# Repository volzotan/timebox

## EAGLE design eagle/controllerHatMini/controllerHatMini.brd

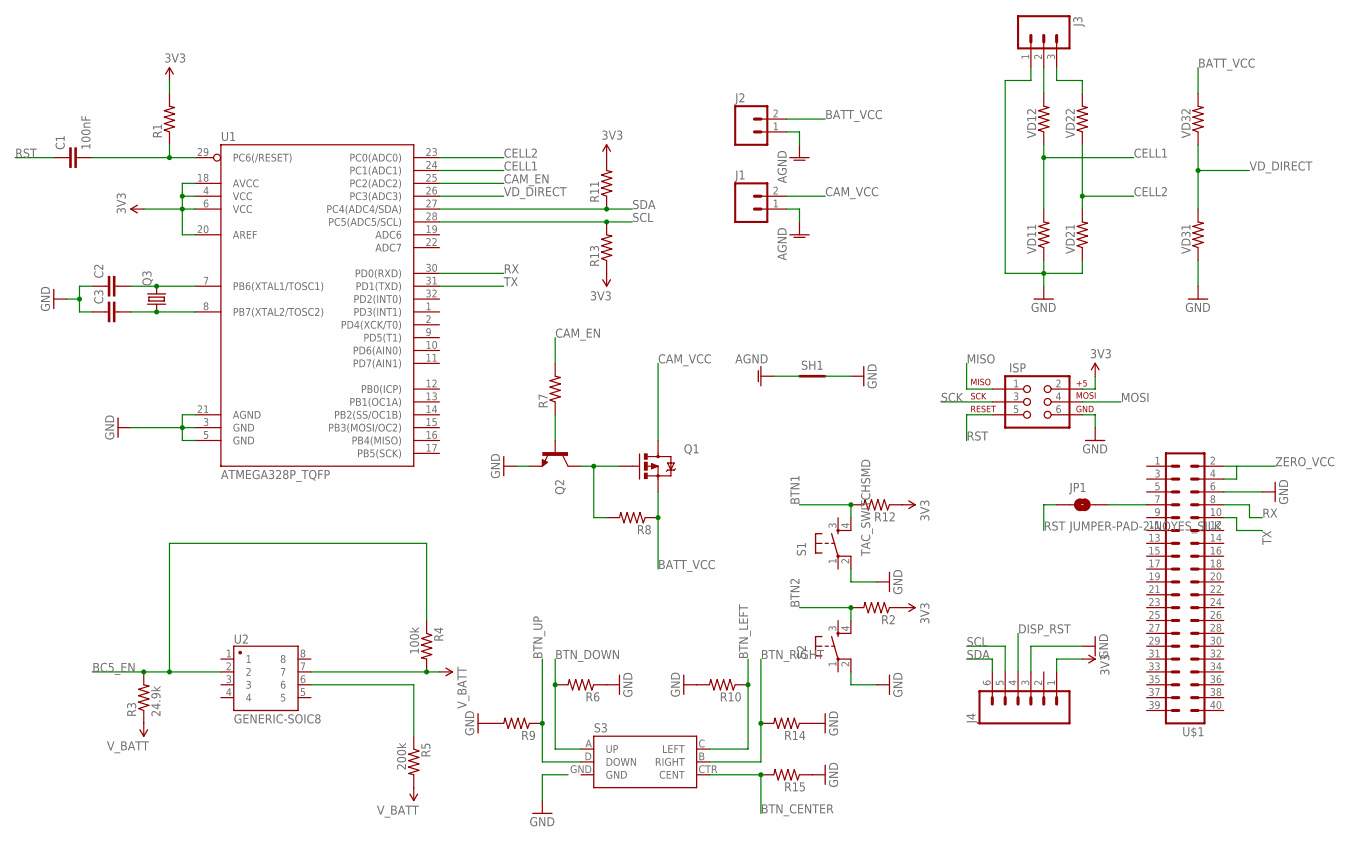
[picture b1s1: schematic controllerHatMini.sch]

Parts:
C1: 100nF; 1206
C2, C3: CAP1206; 1206
ISP: AVR_SPI_PRG_6PTH; 2X3
J1, J2: M023.5MM_LOCK; SCREWTERMINAL-3.5MM-2_LOCK
J3: M03LOCK; 1X03_LOCK
J4: M06LOCK; 1X06_LOCK
JP1: JUMPER-PAD-2-NOYES_SILK; PAD-JUMPER-2-NO_YES_SILK
Q1: MOSFET-PCHANNELNDP6020P_20V_24A_LOW_VGS_TH; TO220V
Q2: TRANSISTOR_NPN2N3904; TO-92
Q3: CRYSTALMM20SS; MM20SS
R1, R2, R6, R7, R8, R9, R10, R11, R12, R13, R14, R15: RESISTOR1206; 1206
R3: 24.9k; 1206
R4: 100k; 1206
R5: 200k; 1206
S1: TAC_SWITCHSMD; TACTILE-PTH
S2: TAC_SWITCHPTH; TACTILE-PTH
S3: JOYSTICK_MINI
SH1: SHORT-HT5; SHORT_TOP-50
U1: ATMEGA328P_TQFP; TQFP32-08
U2: GENERIC-SOIC8; SO08-UNIVERSAL
U$1: PIZERO_THROUGH_HOLE; PIZERO_THOUGH_HOLE
VD11, VD12, VD21, VD22, VD31, VD32: RESISTOR1206; 1206

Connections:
AGND: J1.1, J2.1, SH1.1
BATT_VCC: J2.2, Q1.3 (S), R8.1, VD32.2
BC5_EN: R3.2, R4.1, U2.2
BTN1: R12.2, S1.4
BTN2: R2.2, S2.4
BTN_CENTER: R15.2, S3.CTR (CENT)
BTN_DOWN: R6.2, S3.A (UP)
BTN_LEFT: R10.1, S3.C (LEFT)
BTN_RIGHT: R14.2, S3.B (RIGHT)
BTN_UP: R9.1, S3.D (DOWN)
CAM_EN: R7.2, U1.25 (PC2(ADC2))
CAM_VCC: J1.2, Q1.2 (D)
CELL1: U1.24 (PC1(ADC1)), VD11.2, VD12.1
CELL2: U1.23 (PC0(ADC0)), VD21.2, VD22.1
DISP_RST: J4.4
GND: C2.1, C3.1, ISP.6, J3.1, J4.3, Q2.1 (E), R6.1, R9.2, R10.2, R14.1, R15.1, S1.2, S2.2, SH1.2, U1.3 (GND), U1.5 (GND), U1.21 (AGND), U$1.6, VD11.1, VD21.1, VD31.1
MISO: ISP.1
MOSI: ISP.4
unnamed: J3.3, VD22.2
unnamed: J3.2, VD12.2
unnamed: C1.2, R1.1, U1.29 (PC6(/RESET))
unnamed: Q2.2 (B), R7.1
unnamed: C3.2, Q3.1, U1.8 (PB7(XTAL2/TOSC2))
unnamed: C2.2, Q3.4 (2), U1.7 (PB6(XTAL1/TOSC1))
unnamed: JP1.2, U$1.7
unnamed: Q1.1 (G), Q2.3 (C), R8.2
unnamed: R5.1, U2.6
RST: C1.1, ISP.5, JP1.1
RX: U1.30 (PD0(RXD)), U$1.8
SCK: ISP.3
SCL: J4.5, R13.2, U1.28 (PC5(ADC5/SCL))
SDA: J4.6, R11.1, U1.27 (PC4(ADC4/SDA))
TX: U1.31 (PD1(TXD)), U$1.10
VCC: ISP.2, J4.1, R1.2, R2.1, R11.2, R12.1, R13.1, U1.4 (VCC), U1.6 (VCC), U1.18 (AVCC), U1.20 (AREF)
VD_DIRECT: U1.26 (PC3(ADC3)), VD31.2, VD32.1
V_BATT: R3.1, R4.2, R5.2, U2.7
ZERO_VCC: U$1.2

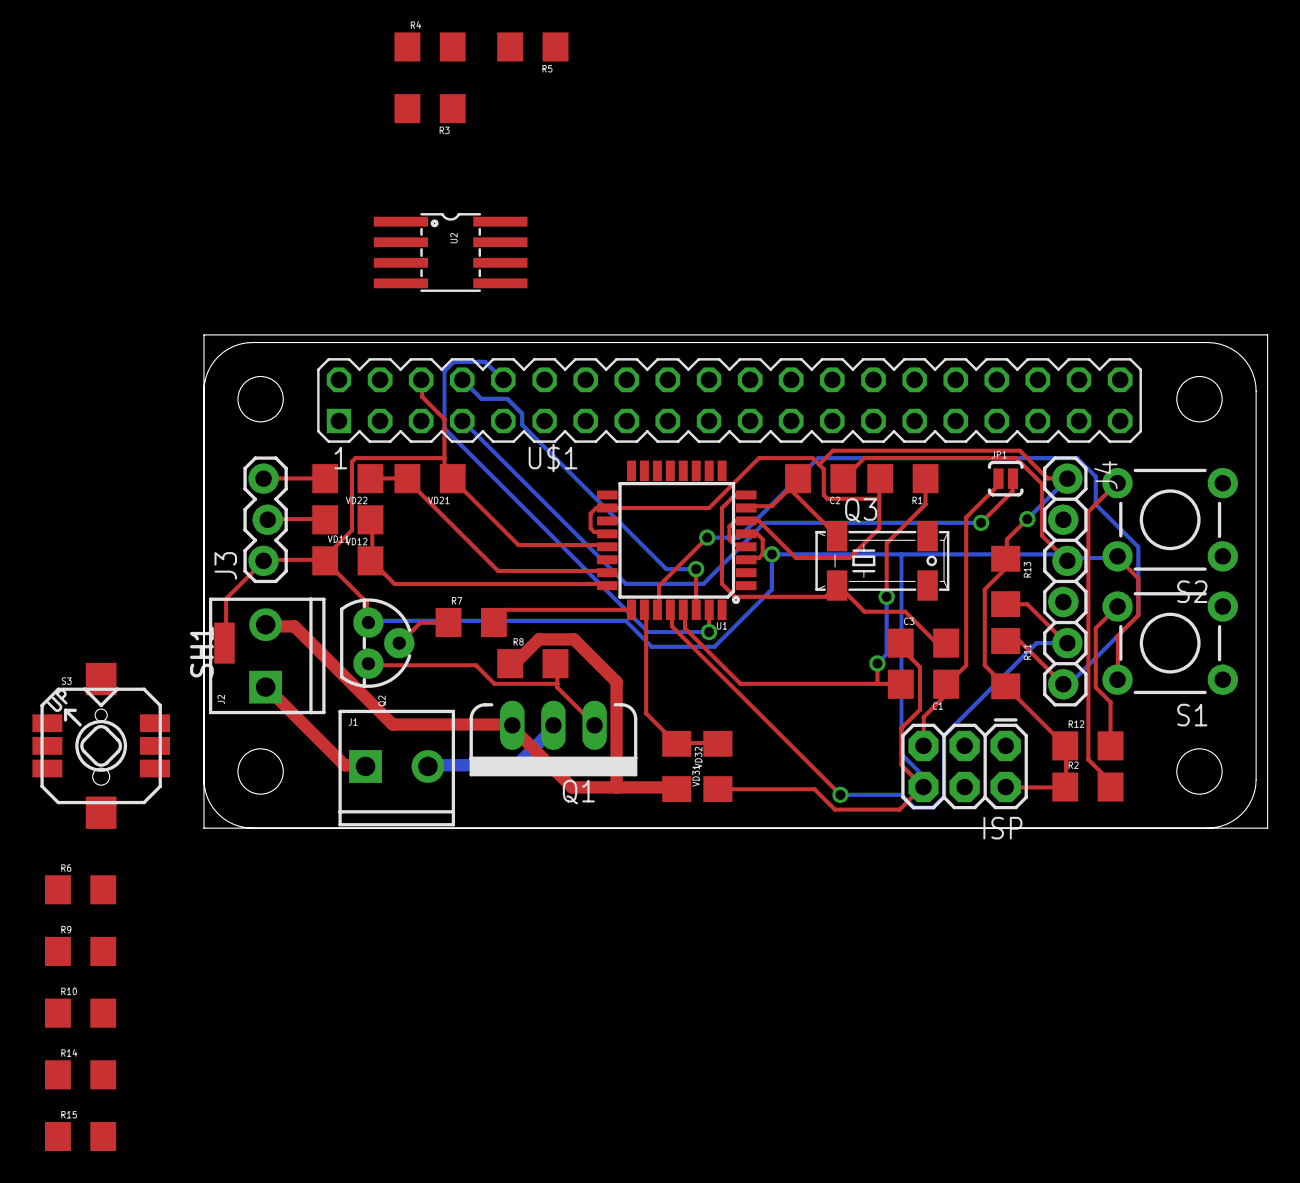
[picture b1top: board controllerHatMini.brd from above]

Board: 2 copper layers, 65.7 x 30.5 mm, 40 parts (0 on the bottom side), 32 nets.

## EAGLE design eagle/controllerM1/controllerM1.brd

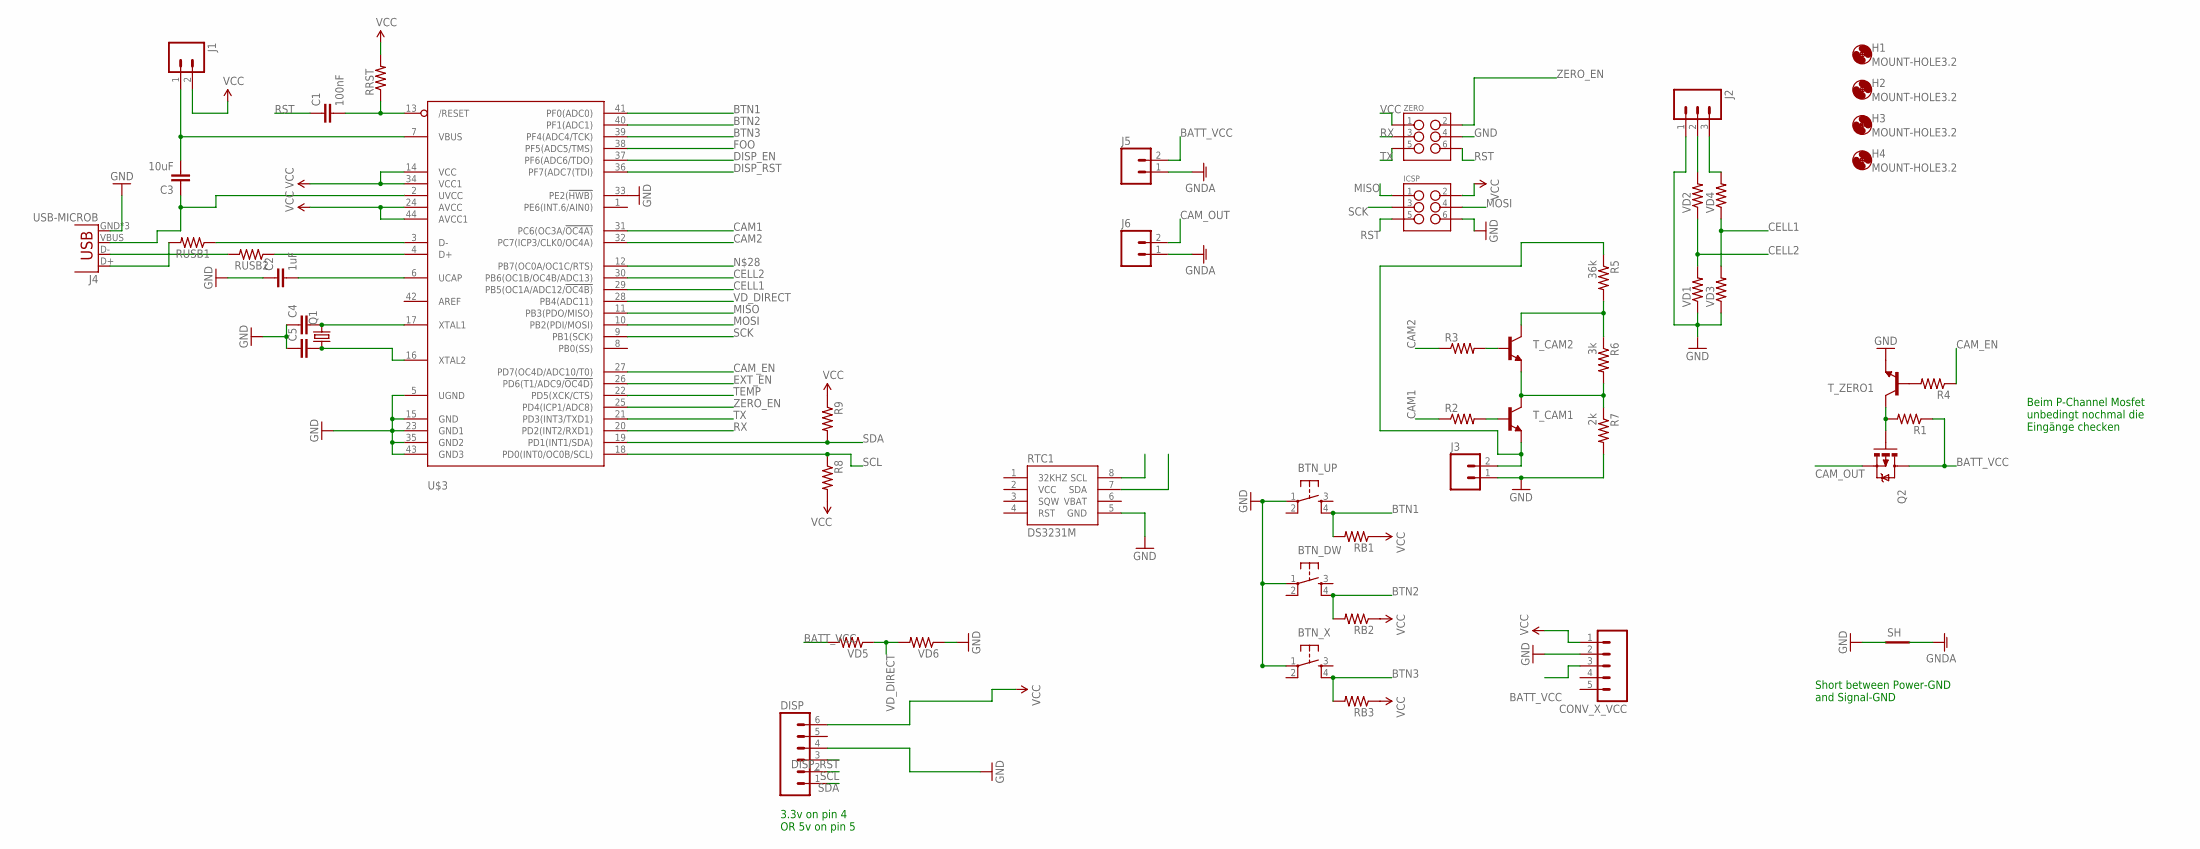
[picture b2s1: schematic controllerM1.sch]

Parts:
BTN_DW: TAC_SWITCHPTH; TACTILE-PTH
BTN_UP: TAC_SWITCHPTH; TACTILE-PTH
BTN_X: TAC_SWITCHPTH; TACTILE-PTH
C1: 100nF; 1206
C2: 1uF; 1206
C3: 10uF; 1206
C4, C5: CAP1206; 1206
CONV_X_VCC: M05LOCK; 1X05_LOCK
DISP: M06FEMALE_LOCK; 1X06_FEMALE_LOCK.010
H1, H2, H3, H4: MOUNT-HOLE3.2; 3,2
ICSP: M03X2FEMALE; 2X3
J1, J3: M02LOCK; 1X02_LOCK
J2: M03LOCK; 1X03_LOCK
J4: USB-MICROB
J5, J6: M023.5MM_LOCK; SCREWTERMINAL-3.5MM-2_LOCK
Q1: CRYSTALHC49S; HC49/S
Q2: MOSFET-PCHANNELFQP27P06; TO220V
R1, R2, R3, R4, R8, R9: RESISTOR1206; 1206
R5: 36k; 1206
R6: 3k; 1206
R7: 2k; 1206
RB1, RB2, RB3: RESISTOR1206; 1206
RRST: RESISTOR1206; 1206
RTC1: DS3231M; SOIC8
RUSB1, RUSB2: RESISTOR1206; 1206
SH: SHORT-HT5; SHORT_TOP-50
T_CAM1, T_CAM2: TRANSISTOR_NPN2N3904; TO-92
T_ZERO1: TRANSISTOR_NPN2N3904; TO-92
U$3: ATMEGA32U4-AU; TQFP44
VD1, VD2, VD3, VD4, VD5, VD6: RESISTOR1206; 1206
ZERO: M03X2FEMALE; 2X3

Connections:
BATT_VCC: CONV_X_VCC.3, J5.2, Q2.2 (D), R1.1, VD5.2
BTN1: BTN_UP.4, RB1.2, U$3.41 (PF0(ADC0))
BTN2: BTN_DW.4, RB2.2, U$3.40 (PF1(ADC1))
BTN3: BTN_X.4, RB3.2, U$3.39 (PF4(ADC4/TCK))
CAM1: R2.1, U$3.31 (PC6(OC3A/!OC4A))
CAM2: R3.1, U$3.32 (PC7(ICP3/CLK0/OC4A))
CAM_EN: R4.1, U$3.27 (PD7(OC4D/ADC10/T0))
CAM_OUT: J6.2, Q2.3 (S)
CELL1: U$3.29 (PB5(OC1A/ADC12/!OC4B)), VD3.2, VD4.1
CELL2: U$3.30 (PB6(OC1B/OC4B/ADC13)), VD1.2, VD2.1
DISP_EN: U$3.37 (PF6(ADC6/TDO))
DISP_RST: DISP.3, U$3.36 (PF7(ADC7(TDI))
EXT_EN: U$3.26 (PD6(T1/ADC9/!OC4D))
FOO: U$3.38 (PF5(ADC5/TMS))
GND: BTN_DW.1, BTN_UP.1, BTN_X.1, C2.1, C4.1, C5.1, CONV_X_VCC.2, DISP.4, ICSP.6, J2.1, J3.1, J4.GND, J4.MT1 (GND), J4.MT2 (GND), R7.2, RTC1.5 (GND), SH.1, T_ZERO1.1 (E), U$3.5 (UGND), U$3.15 (GND), U$3.23 (GND1), U$3.33 (PE2(!HWB)), U$3.35 (GND2), U$3.43 (GND3), VD1.1, VD3.1, VD6.1, ZERO.4
GNDA: J5.1, J6.1, SH.2
MISO: ICSP.1, U$3.11 (PB3(PDO/MISO))
MOSI: ICSP.4, U$3.10 (PB2(PDI/MOSI))
unnamed: C1.2, RRST.1, U$3.13 (/RESET)
unnamed: J2.3, VD4.2
unnamed: J2.2, VD2.2
unnamed: RUSB1.1, U$3.3 (D-)
unnamed: RUSB2.1, U$3.4 (D+)
unnamed: J3.2, R5.1, T_CAM1.1 (E)
unnamed: R4.2, T_ZERO1.2 (B)
unnamed: C4.2, Q1.2, U$3.17 (XTAL1)
unnamed: C5.2, Q1.1, U$3.16 (XTAL2)
unnamed: C3.2, J1.1, U$3.7 (VBUS)
unnamed: R6.2, R7.1, T_CAM1.3 (C), T_CAM2.1 (E)
unnamed: R5.2, R6.1, T_CAM2.3 (C)
unnamed: J4.D+, RUSB1.2
unnamed: J4.D-, RUSB2.2
unnamed: R2.2, T_CAM1.2 (B)
unnamed: R3.2, T_CAM2.2 (B)
unnamed: C2.2, U$3.6 (UCAP)
unnamed: Q2.1 (G), R1.2, T_ZERO1.3 (C)
unnamed: C3.1, J4.VBUS, U$3.2 (UVCC)
RST: C1.1, ICSP.5, ZERO.6
RX: U$3.20 (PD2(INT2/RXD1)), ZERO.3
SCK: ICSP.3, U$3.9 (PB1(SCK))
SCL: DISP.2, R8.1, RTC1.8 (SCL), U$3.18 (PD0(INT0/OC0B/SCL))
SDA: DISP.1, R9.2, RTC1.7 (SDA), U$3.19 (PD1(INT1/SDA))
TEMP: U$3.22 (PD5(XCK/CTS))
TX: U$3.21 (PD3(INT3/TXD1)), ZERO.5
VBAT: RTC1.6 (VBAT)
VCC: CONV_X_VCC.1, DISP.6, ICSP.2, J1.2, R8.2, R9.1, RB1.1, RB2.1, RB3.1, RRST.2, RTC1.2 (VCC), U$3.14 (VCC), U$3.24 (AVCC), U$3.34 (VCC1), U$3.44 (AVCC1), ZERO.1
VD_DIRECT: U$3.28 (PB4(ADC11)), VD5.1, VD6.2
ZERO_EN: U$3.25 (PD4(ICP1/ADC8)), ZERO.2

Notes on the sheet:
3.3v on pin 4 OR 5v on pin 5
Short between Power-GND and Signal-GND
Beim P-Channel Mosfet unbedingt nochmal die Eingänge checken

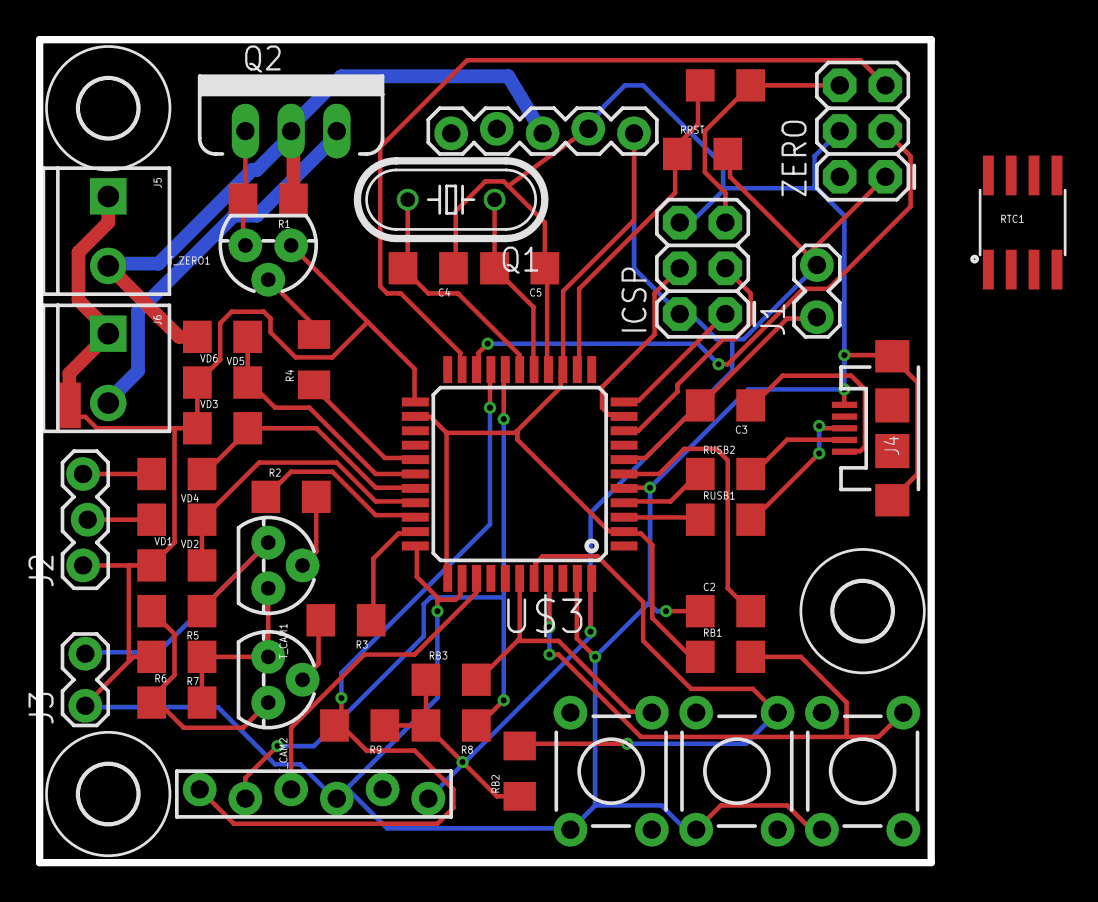
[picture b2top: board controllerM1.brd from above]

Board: 2 copper layers, 49.5 x 45.7 mm, 51 parts (0 on the bottom side), 43 nets.

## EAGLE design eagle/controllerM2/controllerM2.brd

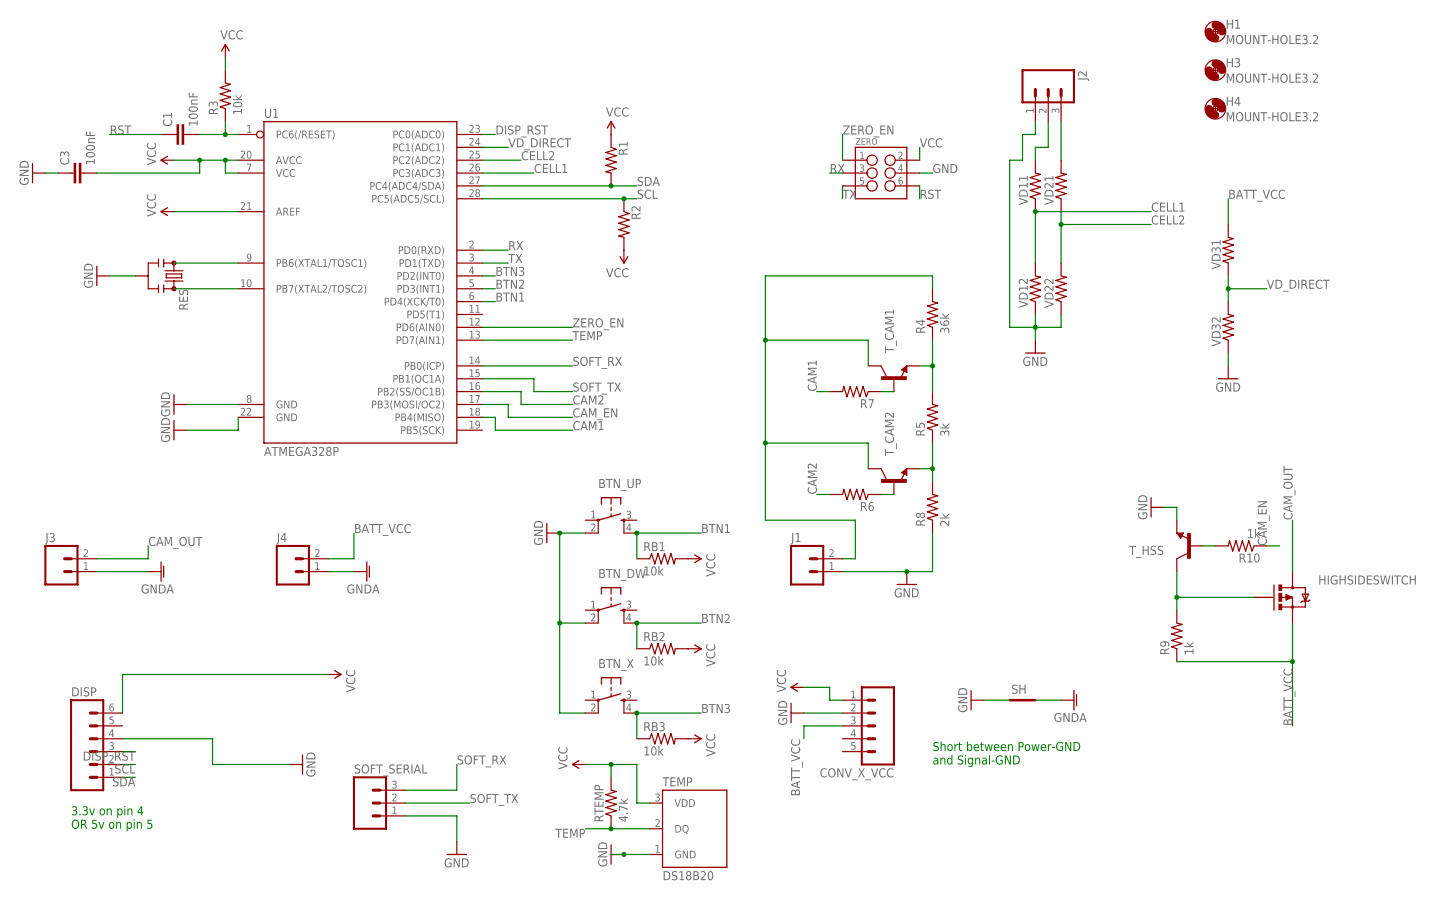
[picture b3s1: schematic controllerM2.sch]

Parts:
BTN_DW: TAC_SWITCHPTH; TACTILE-PTH
BTN_UP: TAC_SWITCHPTH; TACTILE-PTH
BTN_X: TAC_SWITCHPTH; TACTILE-PTH
C1, C3: 100nF; CAP-PTH-SMALL
CONV_X_VCC: M05LOCK; 1X05_LOCK
DISP: M06FEMALE_LOCK; 1X06_FEMALE_LOCK.010
H1, H3, H4: MOUNT-HOLE3.2; 3,2
HIGHSIDESWITCH: MOSFET-PCHANNELNDP6020P_20V_24A_LOW_VGS_TH; TO220V
J1: M02LOCK; 1X02_LOCK
J2: M03LOCK; 1X03_LOCK
J3, J4: M023.5MM_LOCK; SCREWTERMINAL-3.5MM-2_LOCK
R1, R2, R6, R7: RESISTORAXIAL-0.3; AXIAL-0.3
R3: 10k; AXIAL-0.3
R4: 36k; AXIAL-0.3
R5: 3k; AXIAL-0.3
R8: 2k; AXIAL-0.3
R9, R10: 1k; AXIAL-0.3
RB1, RB2, RB3: 10k; AXIAL-0.3
RES: RESONATORPTH; RESONATOR-PTH
RTEMP: 4.7k; AXIAL-0.3
SH: SHORT-HT5; SHORT_TOP-50
SOFT_SERIAL: M03LOCK; 1X03_LOCK
TEMP: DS18B20; TO-92-AMMO
T_CAM1, T_CAM2: TRANSISTOR_NPN2N3904; TO-92
T_HSS: TRANSISTOR_NPN2N3904; TO-92
U1: ATMEGA328P; DIL28-3
VD11, VD12, VD21, VD22, VD31, VD32: RESISTORAXIAL-0.3; AXIAL-0.3
ZERO: M03X2FEMALE; 2X3

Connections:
BATT_VCC: CONV_X_VCC.3, HIGHSIDESWITCH.3 (S), J4.2, R9.P$1 (1), VD31.P$2 (2)
BTN1: BTN_UP.4, RB1.P$1 (1), U1.6 (PD4(XCK/T0))
BTN2: BTN_DW.4, RB2.P$1 (1), U1.5 (PD3(INT1))
BTN3: BTN_X.4, RB3.P$1 (1), U1.4 (PD2(INT0))
CAM1: R7.P$2 (2), U1.18 (PB4(MISO))
CAM2: R6.P$2 (2), U1.16 (PB2(SS/OC1B))
CAM_EN: R10.P$1 (1), U1.17 (PB3(MOSI/OC2))
CAM_OUT: HIGHSIDESWITCH.2 (D), J3.2
CELL1: U1.26 (PC3(ADC3)), VD11.P$1 (1), VD12.P$2 (2)
CELL2: U1.25 (PC2(ADC2)), VD21.P$1 (1), VD22.P$2 (2)
DISP_RST: DISP.3, U1.23 (PC0(ADC0))
GND: BTN_DW.2, BTN_UP.2, BTN_X.2, C3.1, CONV_X_VCC.2, DISP.4, J1.1, J2.1, R8.P$1 (1), RES.2, SH.1, SOFT_SERIAL.1, TEMP.1 (GND), T_HSS.1 (E), U1.8 (GND), U1.22 (GND), VD12.P$1 (1), VD22.P$1 (1), VD32.P$1 (1), ZERO.4
GNDA: J3.1, J4.1, SH.2
unnamed: C1.2, R3.P$1 (1), U1.1 (PC6(/RESET))
unnamed: J2.2, VD11.P$2 (2)
unnamed: R7.P$1 (1), T_CAM1.2 (B)
unnamed: J2.3, VD21.P$2 (2)
unnamed: J1.2, R4.P$2 (2), T_CAM1.3 (C), T_CAM2.3 (C)
unnamed: RES.3, U1.10 (PB7(XTAL2/TOSC2))
unnamed: RES.1, U1.9 (PB6(XTAL1/TOSC1))
unnamed: R6.P$1 (1), T_CAM2.2 (B)
unnamed: R10.P$2 (2), T_HSS.2 (B)
unnamed: HIGHSIDESWITCH.1 (G), R9.P$2 (2), T_HSS.3 (C)
unnamed: R4.P$1 (1), R5.P$2 (2), T_CAM1.1 (E)
unnamed: R5.P$1 (1), R8.P$2 (2), T_CAM2.1 (E)
RST: C1.1, ZERO.6
RX: U1.2 (PD0(RXD)), ZERO.3
SCL: DISP.2, R2.P$1 (1), U1.28 (PC5(ADC5/SCL))
SDA: DISP.1, R1.P$2 (2), U1.27 (PC4(ADC4/SDA))
SOFT_RX: SOFT_SERIAL.3, U1.14 (PB0(ICP))
SOFT_TX: SOFT_SERIAL.2, U1.15 (PB1(OC1A))
TEMP: RTEMP.P$1 (1), TEMP.2 (DQ), U1.13 (PD7(AIN1))
TX: U1.3 (PD1(TXD)), ZERO.5
VCC: C3.2, CONV_X_VCC.1, DISP.6, R1.P$1 (1), R2.P$2 (2), R3.P$2 (2), RB1.P$2 (2), RB2.P$2 (2), RB3.P$2 (2), RTEMP.P$2 (2), TEMP.3 (VDD), U1.7 (VCC), U1.20 (AVCC), U1.21 (AREF), ZERO.2
VD_DIRECT: U1.24 (PC1(ADC1)), VD31.P$1 (1), VD32.P$2 (2)
ZERO_EN: U1.12 (PD6(AIN0)), ZERO.1

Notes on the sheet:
3.3v on pin 4 OR 5v on pin 5
Short between Power-GND and Signal-GND

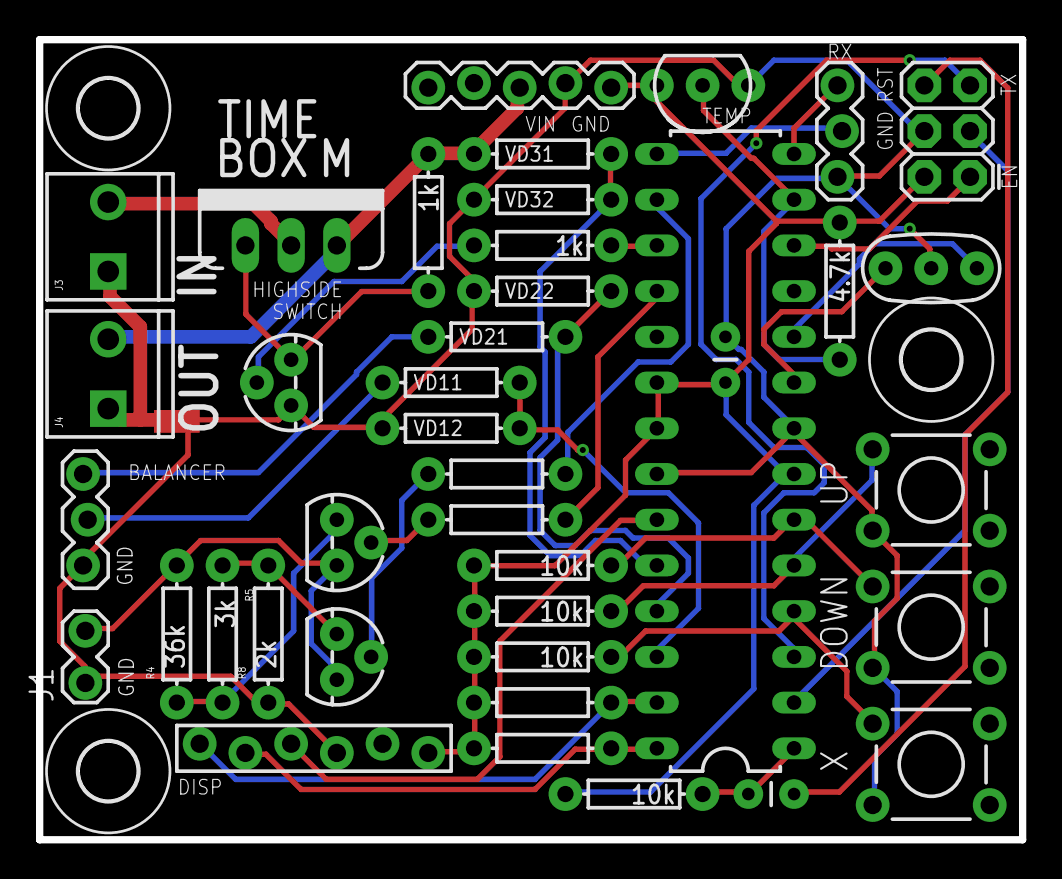
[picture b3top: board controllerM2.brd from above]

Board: 2 copper layers, 54.6 x 44.5 mm, 44 parts (0 on the bottom side), 36 nets.

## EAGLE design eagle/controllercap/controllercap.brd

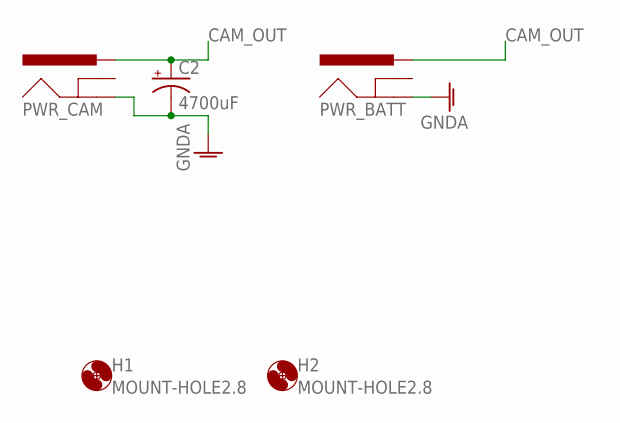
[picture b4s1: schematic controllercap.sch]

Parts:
C2: 4700uF; CPOL-RADIAL-1000UF-63V
H1, H2: MOUNT-HOLE2.8; 2,8
PWR_BATT: POWER_JACKPTH_BREAD; POWER_JACK_PTH_BREAD
PWR_CAM: POWER_JACKPTH_BREAD; POWER_JACK_PTH_BREAD

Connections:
CAM_OUT: C2.1 (+), PWR_BATT.PWR, PWR_CAM.PWR
GNDA: C2.2 (-), PWR_BATT.GND, PWR_CAM.GND

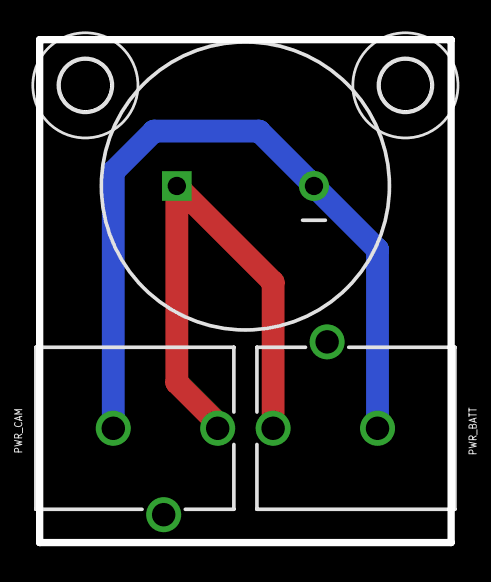
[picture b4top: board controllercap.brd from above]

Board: 2 copper layers, 22.9 x 27.9 mm, 5 parts (0 on the bottom side), 2 nets.

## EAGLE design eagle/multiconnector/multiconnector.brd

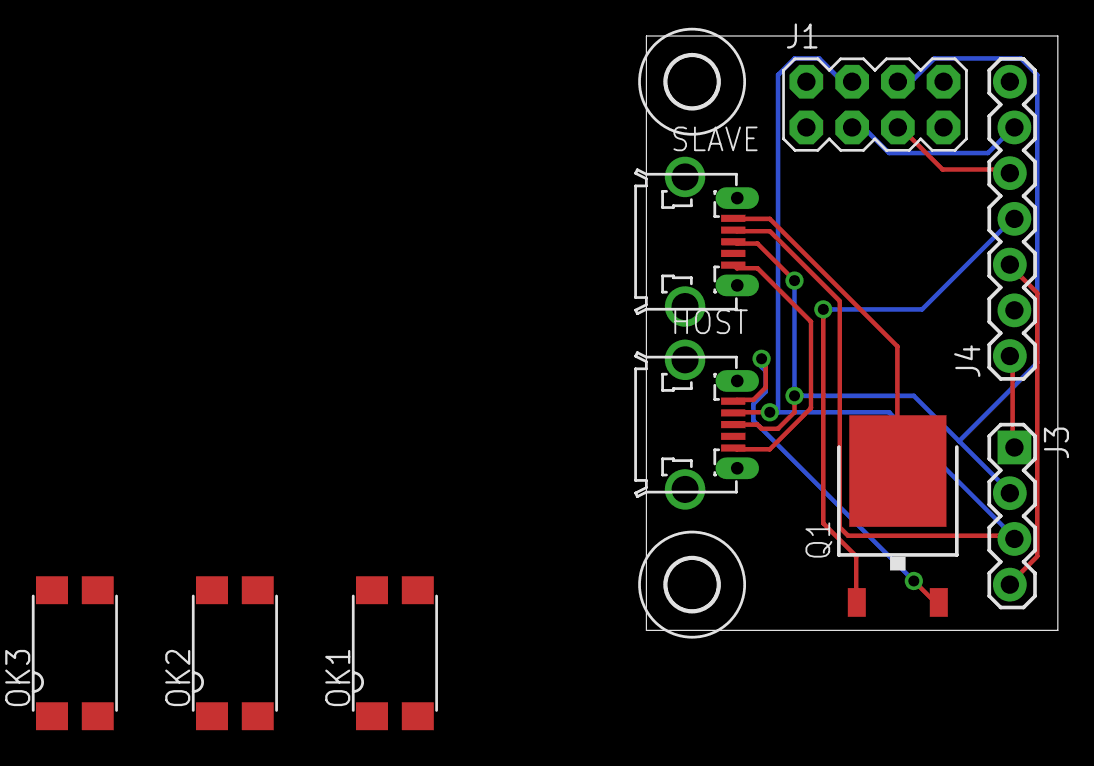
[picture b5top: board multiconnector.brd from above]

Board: 2 copper layers, 22.9 x 33.0 mm, 11 parts (0 on the bottom side), 10 nets.

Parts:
H1, H2: MOUNT-HOLE2.8; 2,8
HOST: ZX62D-B-5PA8
J1: 2X4
J3: 1X04_LOCK
J4: 1X07_LOCK
OK1, OK2, OK3: LTV816S; SMD4
Q1: FDD4141TO252; TO252
SLAVE: ZX62D-B-5PA8

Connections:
CAM2: J1.3, J4.6
CAM3: J1.5, J4.5
D+: HOST.2, J1.4, J3.3, SLAVE.2
D-: HOST.3, J1.6, J3.2, SLAVE.3
GND: J3.1, J4.1
HOST_VCC: HOST.1, Q1.2
unnamed: HOST.5, SLAVE.5
SLAVE_VCC: Q1.3, SLAVE.1
VCC: J3.4, J4.3
VCC_EN: J4.4, Q1.1

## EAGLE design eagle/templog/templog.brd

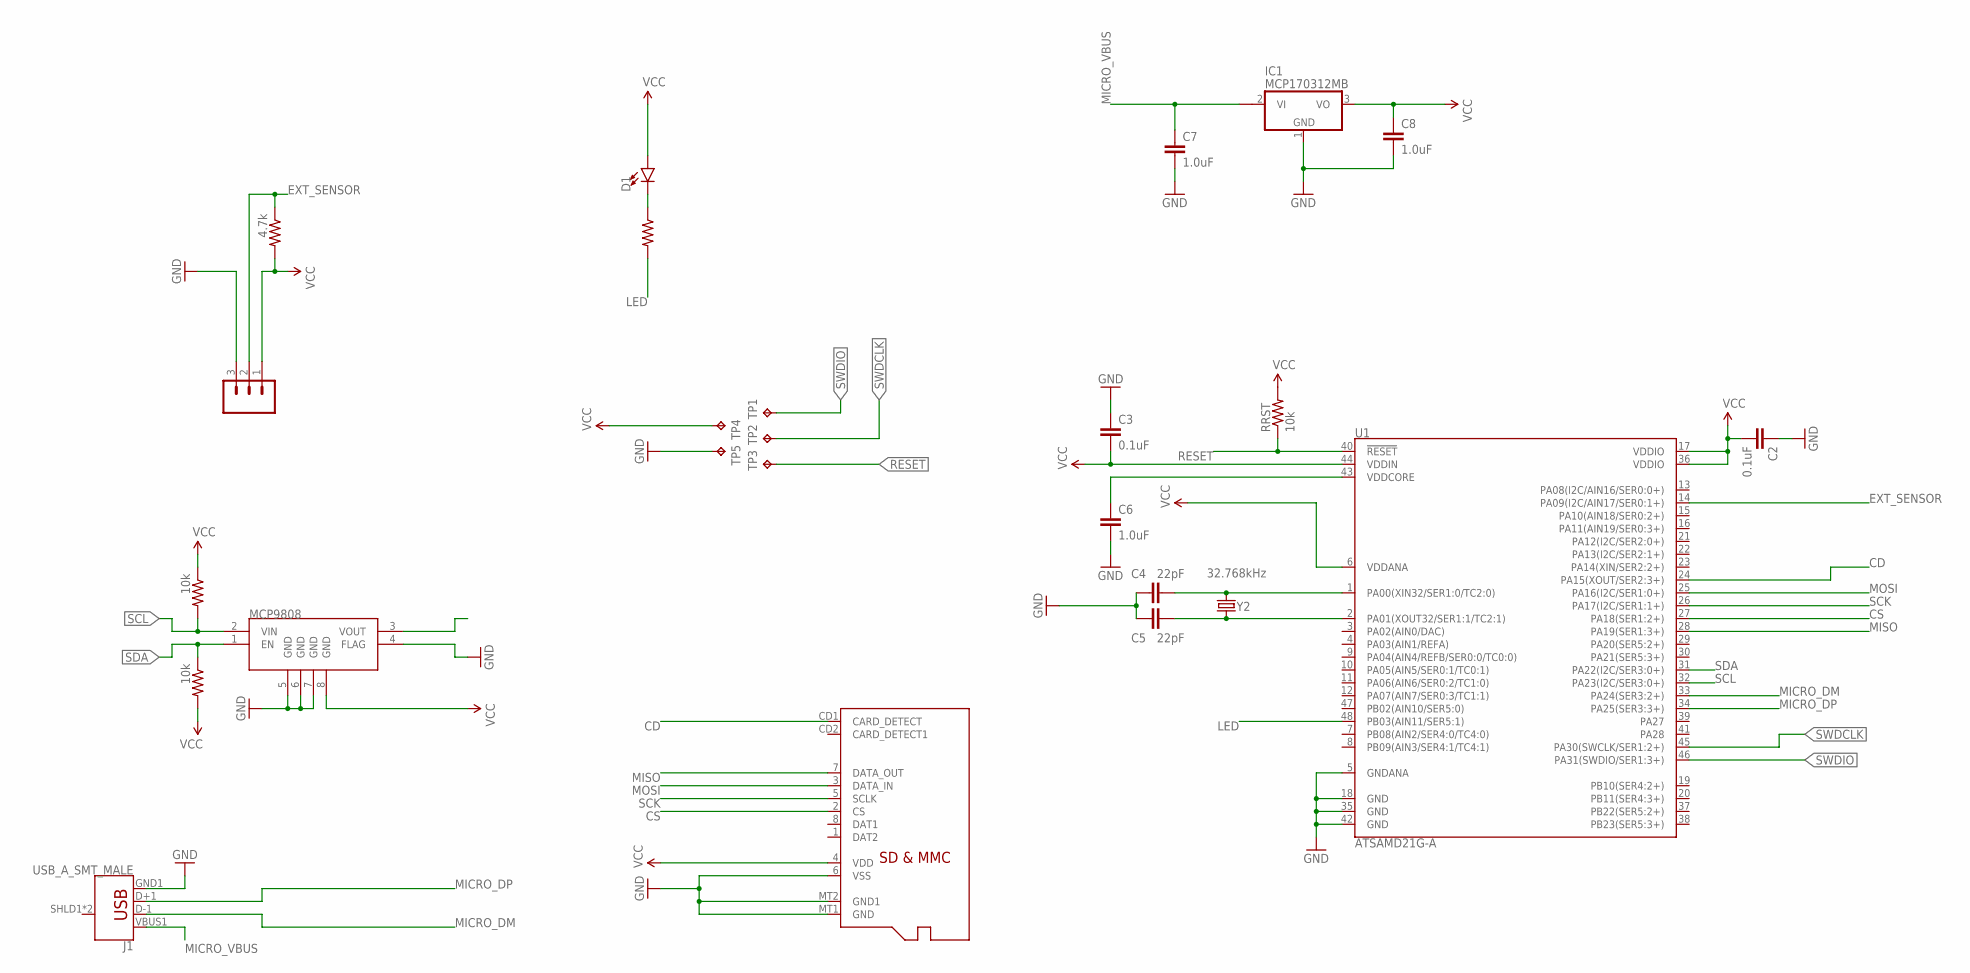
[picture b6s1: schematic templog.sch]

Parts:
C2, C3: 0.1uF; 0805
C4, C5: 22pF; 0805
C6, C7, C8: 1.0uF; 0805
D1: LED1206; LED-1206
IC1: MCP170312MB; SOT89
J1: USB_A_SMT_MALE; USB-A-SMT-MALE
J2: CONN_03SMD; 1X03-1MM-RA
MCP9808: V_REG_MIC5216; MSOP8
RRST: 10k; 0805
R_I2C_1, R_I2C_2: 10k; 0805
R_I2C_3: 4.7k; 0805
R_I2C_4: RESISTOR0805-RES; 0805
TP1, TP2, TP3, TP4, TP5: TPB1,27; B1,27
U1: ATSAMD21G-A; TQFP-48
U$1: MICROSD
Y2: 32.768kHz; CRYSTAL-SMD-3.2X1.5MM

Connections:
CD: U1.24 (PA15(XOUT/SER2:3+)), U$1.CD1 (CARD_DETECT)
CS: U1.27 (PA18(SER1:2+)), U$1.2 (CS)
EXT_SENSOR: J2.2, R_I2C_3.1, U1.14 (PA09(I2C/AIN17/SER0:1+))
GND: C2.1, C3.1, C4.1, C5.1, C6.2, C7.2, C8.2, IC1.1 (GND), J1.GND1 (GND), J2.3, MCP9808.4 (FLAG), MCP9808.5 (GND), MCP9808.6 (GND), MCP9808.7 (GND), TP5.TP, U1.5 (GNDANA), U1.18 (GND), U1.35 (GND), U1.42 (GND), U$1.6 (VSS), U$1.MT1 (GND), U$1.MT2 (GND1)
LED: R_I2C_4.2, U1.48 (PB03(AIN11/SER5:1))
MICRO_DM: J1.D-1 (D-), U1.33 (PA24(SER3:2+))
MICRO_DP: J1.D+1 (D+), U1.34 (PA25(SER3:3+))
MICRO_VBUS: C7.1, IC1.2@1 (VI1), J1.VBUS1 (VBUS)
MISO: U1.28 (PA19(SER1:3+)), U$1.7 (DATA_OUT)
MOSI: U1.25 (PA16(I2C/SER1:0+)), U$1.3 (DATA_IN)
unnamed: C6.1, U1.43 (VDDCORE)
unnamed: D1.C, R_I2C_4.1
unnamed: C4.2, U1.1 (PA00(XIN32/SER1:0/TC2:0)), Y2.P$2 (2)
unnamed: C5.2, U1.2 (PA01(XOUT32/SER1:1/TC2:1)), Y2.P$1 (1)
RESET: RRST.1, TP3.TP, U1.40 (!RESET!)
SCK: U1.26 (PA17(I2C/SER1:1+)), U$1.5 (SCLK)
SCL: MCP9808.2 (VIN), R_I2C_1.2, U1.32 (PA23(I2C/SER3:0+))
SDA: MCP9808.1 (EN), R_I2C_2.1, U1.31 (PA22(I2C/SER3:0+))
SWDCLK: TP2.TP, U1.45 (PA30(SWCLK/SER1:2+))
SWDIO: TP1.TP, U1.46 (PA31(SWDIO/SER1:3+))
VCC: C2.2, C3.2, C8.1, D1.A, IC1.3 (VO), J2.1, MCP9808.8 (GND), RRST.2, R_I2C_1.1, R_I2C_2.2, R_I2C_3.2, TP4.TP, U1.6 (VDDANA), U1.17 (VDDIO), U1.36 (VDDIO), U1.44 (VDDIN), U$1.4 (VDD)

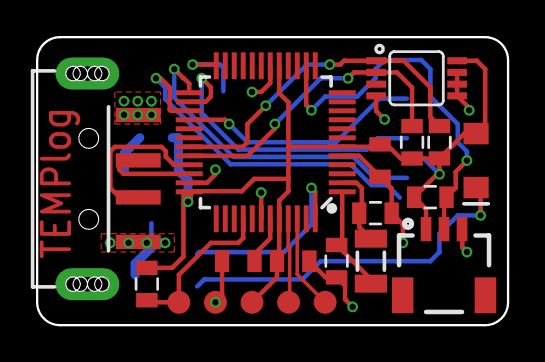
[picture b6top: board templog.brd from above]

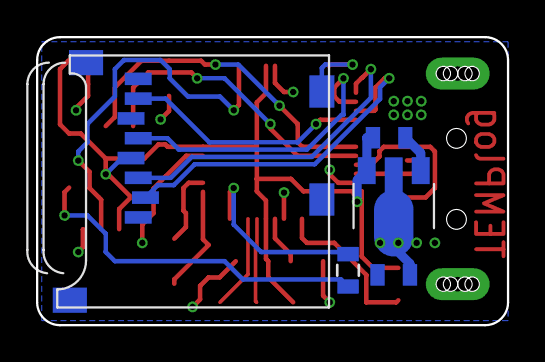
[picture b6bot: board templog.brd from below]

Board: 2 copper layers, 26.2 x 16.0 mm, 25 parts (5 on the bottom side), 21 nets.

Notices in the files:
parts and their libraries:
SparkFun-DigitalIC: Licensing: Creative Commons ShareAlike 4.0 International - https://creativecommons.org/licenses/by-sa/4.0
